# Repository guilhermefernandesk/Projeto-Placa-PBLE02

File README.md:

# Projeto-Placa-PBLE02
O projeto consiste na montagem de uma placa realizada por alunos da unifei. Bem como suas correções necessárias e simulação de uma aplicação via software na linguagem C.

## Autores:
<ul>
  <li> Eric Makiya Lazanha </li>
  <li> Guilherme Fernandes de Oliveira </li>
  <li> João Luiz de Miranda Cilli </li>
  <li> João Roberto da Silva Couto </li>
</ul>

## Imagens:

## Vídeo apresentação do projeto:
https://drive.google.com/file/d/1amIkBEUgF5RGjeDBrGX1CGrTWx1kXM-I/view?usp=sharing

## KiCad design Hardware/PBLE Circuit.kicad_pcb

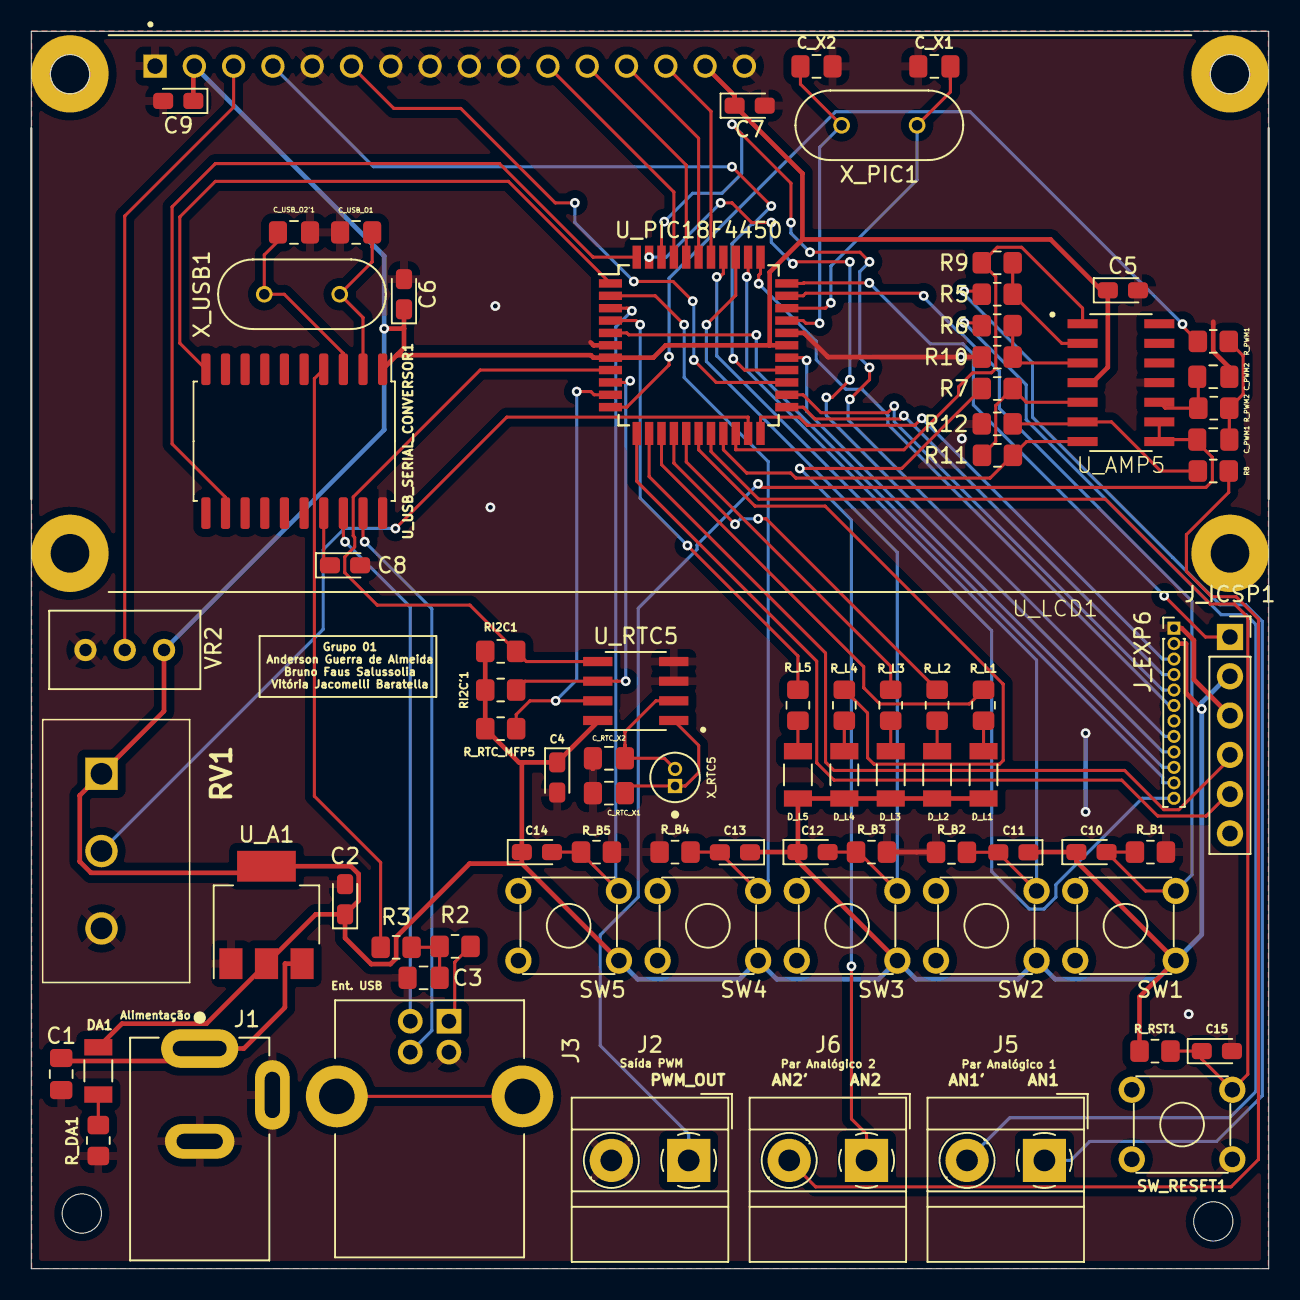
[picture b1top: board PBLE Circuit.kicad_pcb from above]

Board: 2 copper layers, 80.0 x 80.0 mm, 80 parts (0 on the bottom side), 71 nets.

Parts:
C1: 100n; C_0805_2012Metric_Pad1.18x1.45mm_HandSolder
C2, C4, C5, C6, C7, C8, C9, C10, C11, C12, C13, C14, C15: 10u; CP_EIA-2012-15_AVX-P_Pad1.30x1.05mm_HandSolder
C3: 100nF; C_0805_2012Metric_Pad1.18x1.45mm_HandSolder
C_PWM1: 20p; C_0805_2012Metric_Pad1.18x1.45mm_HandSolder
C_PWM2: 39p; C_0805_2012Metric_Pad1.18x1.45mm_HandSolder
C_RTC_X1, C_RTC_X2: 22pF; C_0805_2012Metric_Pad1.18x1.45mm_HandSolder
C_USB_O1, C_USB_O2'1: 22pF; C_0805_2012Metric_Pad1.18x1.45mm_HandSolder
C_X1, C_X2: 15pF; C_0805_2012Metric_Pad1.18x1.45mm_HandSolder
DA1: LED; LTST-C150GKT
D_L1, D_L2, D_L3, D_L4, D_L5: LED; LTST-C150GKT
J1: PJ-002A; CUI_PJ-002A
J2, J5, J6: Screw_Terminal_01x02; TerminalBlock_MetzConnect_Type011_RT05502HBWC_1x02_P5.00mm_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
J3: USB_B; USB_B_Lumberg_2411_02_Horizontal
J_EXP6: Conn_01x12_Male; PinHeader_1x12_P1.00mm_Vertical
J_ICSP1: Conn_01x06; PinSocket_1x06_P2.54mm_Vertical
R2, R5, R6, R7, R8: 10k; R_0805_2012Metric_Pad1.20x1.40mm_HandSolder
R3: 470; R_0805_2012Metric_Pad1.20x1.40mm_HandSolder
R9, R10, R11, R12: 2k4; R_0805_2012Metric_Pad1.20x1.40mm_HandSolder
RI2C1, RI2C'1: 4k7; R_0805_2012Metric_Pad1.20x1.40mm_HandSolder
RV1: R_POT; P160KN-0QC15B100K
R_B1, R_B2, R_B3, R_B4, R_B5: 4k7; R_0805_2012Metric_Pad1.20x1.40mm_HandSolder
R_DA1: 330; R_0805_2012Metric_Pad1.20x1.40mm_HandSolder
R_L1, R_L2, R_L3, R_L4, R_L5: 4k7; R_0805_2012Metric_Pad1.20x1.40mm_HandSolder
R_PWM1, R_PWM2: 20k; R_0805_2012Metric_Pad1.20x1.40mm_HandSolder
R_RST1: 4k7; R_0805_2012Metric_Pad1.20x1.40mm_HandSolder
R_RTC_MFP5: 10k; R_0805_2012Metric_Pad1.20x1.40mm_HandSolder
SW1, SW2, SW3, SW4, SW5: 1825910-6; SW_TH_Tactile_Omron_B3F-10xx
SW_RESET1: 1825910-6; SW_TH_Tactile_Omron_B3F-10xx
U_A1: LD1117S50TR_SOT223; SOT-223-3_TabPin2
U_AMP5: LM324DG
U_LCD1: LCD2X16; JHD162A
U_PIC18F4450: PIC18F4550-IPT; TQFP-44_10x10mm_P0.8mm
U_RTC5: MCP7940N-xSN; MCP7940N
U_USB_SERIAL_CONVERSOR1: MCP2200-I-SO; SOIC-20W_7.5x12.8mm_P1.27mm
VR2: 3296W-1-103RLF; Potentiometer_Bourns_3296W_Vertical
X_PIC1: ATS20A
X_RTC5: AB38T-32.768KHZ; AB38T
X_USB1: ATS12A

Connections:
+5V: C2.1, C4.1, C5.1, C6.1, C7.1, C9.1, C10.1, C11.1, C12.1, C13.1, C14.1, DA1.2 (A), D_L1.2 (A), D_L2.2 (A), D_L3.2 (A), D_L4.2 (A), D_L5.2 (A), J_EXP6.2, J_ICSP1.2, RI2C1.1, RI2C'1.1, RV1.1, R_RST1.1, R_RTC_MFP5.2, SW1.1, SW2.1, SW3.1, SW4.1, SW5.1, U_A1.2 (VO), U_AMP5.4 (VCC), U_LCD1.2 (VDD), U_LCD1.15 (LEDA), U_PIC18F4450.7 (VDD), U_PIC18F4450.28 (VDD), U_RTC5.8 (VCC), U_USB_SERIAL_CONVERSOR1.1 (VDD), VR2.3
/Alimentação/D+: J3.3 (D+), U_USB_SERIAL_CONVERSOR1.19 (D+)
/Alimentação/D-: J3.2 (D-), U_USB_SERIAL_CONVERSOR1.18 (D-)
/Alimentação/MCP_RST: R3.1, U_USB_SERIAL_CONVERSOR1.4 (RST)
/Interação com o usuário/B1: C10.2, R_B1.2, SW1.3, U_PIC18F4450.32 (T1OSO/T13CKI/RC0)
/Interação com o usuário/B2: C11.2, R_B2.2, SW2.3, U_PIC18F4450.35 (~UOE/CCP2/T1OSI/RC1)
/Interação com o usuário/B3: C12.2, R_B3.2, SW3.3, U_PIC18F4450.36 (P1A/CCP1/RC2)
/Interação com o usuário/B4: C13.2, R_B4.2, SW4.3, U_PIC18F4450.2 (SPP4/RD4)
/Interação com o usuário/B5: C14.2, R_B5.2, SW5.3, U_PIC18F4450.3 (P1B/SPP5/RD5)
/Interação com o usuário/L1: R_L1.1, U_PIC18F4450.14 (RB4/AN11/KBI0/CSSPP)
/Interação com o usuário/L2: R_L2.1, U_PIC18F4450.15 (RB5/KBI1/PGM)
/Interação com o usuário/L3: R_L3.1, U_PIC18F4450.16 (RB6/KBI2/PGC)
/Interação com o usuário/L4: R_L4.1, U_PIC18F4450.17 (RB7/KBI3/PGD)
/Interação com o usuário/L5: R_L5.1, U_PIC18F4450.4 (P1C/SPP6/RD6)
/Interação com o usuário/LCD.DB4: U_LCD1.11 (DB4), U_PIC18F4450.41 (SPP3/RD3)
/Interação com o usuário/LCD.DB5: U_LCD1.12 (DB5), U_PIC18F4450.40 (SPP2/RD2)
/Interação com o usuário/LCD.DB6: U_LCD1.13 (DB6), U_PIC18F4450.39 (SPP1/RD1)
/Interação com o usuário/LCD.DB7: U_LCD1.14 (DB7), U_PIC18F4450.38 (SPP0/RD0)
/Interação com o usuário/LCD.E: U_LCD1.6 (E), U_PIC18F4450.25 (CK1SPP/AN5/RE0)
/Interação com o usuário/LCD.RS: U_LCD1.4 (RS), U_PIC18F4450.26 (CK2SPP/AN6/RE1)
/Interação com o usuário/POT.OUT: RV1.2, U_PIC18F4450.21 (RA2/AN2/Vref-/CVref)
/Operação/AN1: R9.1, U_AMP5.1 (OUT1), U_PIC18F4450.20 (RA1/AN1)
/Operação/AN2: R11.1, U_AMP5.7 (OUT2), U_PIC18F4450.19 (RA0/AN0)
/Operação/ICPORTS: J_EXP6.6, U_PIC18F4450.34 ((ICPORTS))
/Operação/ICRST: J_ICSP1.1, U_PIC18F4450.33 ((~ICRST/ICVpp))
/Operação/MFP: R_RTC_MFP5.1, U_PIC18F4450.10 (RB2/AN8/INT2/VMO), U_RTC5.7 (MFP)
/Operação/PWM: R_PWM1.2, U_PIC18F4450.11 (RB3/AN9/CCP2/VPO)
/Operação/RA3: J_EXP6.3, U_PIC18F4450.22 (RA3/AN3/Vref+)
/Operação/RA4: J_EXP6.4, U_PIC18F4450.23 (RA4/T0CKI/C1OUT/RCV)
/Operação/RA5: J_EXP6.5, U_PIC18F4450.24 (RA5/AN4/~SS/HLVDIN/C2OUT)
/Operação/RC4: J_EXP6.8, U_PIC18F4450.42 (VM/D-/RC4)
/Operação/RC5: J_EXP6.9, U_PIC18F4450.43 (VP/D+/RC5)
/Operação/RD7: J_EXP6.11, U_PIC18F4450.5 (P1D/SPP7/RD7)
/Operação/RE2: J_EXP6.10, U_PIC18F4450.27 (OESPP/AN7/RE2)
/Operação/SCL: RI2C'1.2, U_PIC18F4450.9 (RB1/AN10/INT1/SCK/SCL), U_RTC5.6 (SCL)
/Operação/SDA: RI2C1.2, U_PIC18F4450.8 (RB0/AN12/INT0/FLT0/SDI/SDA), U_RTC5.5 (SDA)
/Operação/VUSB': J_EXP6.12, U_PIC18F4450.37 (VUSB)
AN1: J5.1, R5.2
AN1': J5.2, R6.2
AN2: J6.1, R7.2
AN2': J6.2, R8.2
A_IN+: R6.1, R10.2, U_AMP5.3 (IN1)
A_IN-: R5.1, R9.2, U_AMP5.2 (IN1)
B_IN+: R8.1, R12.2, U_AMP5.6 (IN2)
B_IN-: R7.1, R11.2, U_AMP5.5 (IN2)
CLK0: C_X1.1, U_PIC18F4450.31 (RA6/OSC2/CLKO), X_PIC1.1
CLK1: C_X2.1, U_PIC18F4450.30 (OSC1/CLKI), X_PIC1.2
C_IN+: C_PWM2.2, R_PWM2.1, U_AMP5.10 (IN3)
GNDREF: C1.2, C2.2, C3.1, C4.2, C5.2, C6.2, C7.2, C8.2, C9.2, C15.2, C_PWM2.1, C_RTC_X1.2, C_RTC_X2.2, C_USB_O1.2, C_USB_O2'1.2, C_X1.2, C_X2.2, J1.2, J1.3, J2.2, J3.4 (GND), J_EXP6.1, J_ICSP1.3, R10.1, R12.1, RV1.3, R_B1.1, R_B2.1, R_B3.1, R_B4.1, R_B5.1, R_DA1.2, SW_RESET1.1, U_A1.1 (GND), U_AMP5.11 (VEE,_GND), U_LCD1.1 (VSS), U_LCD1.5 (R/W), U_LCD1.7 (DB0), U_LCD1.8 (DB1), U_LCD1.9 (DB2), U_LCD1.10 (DB3), U_LCD1.16 (LEDK), U_PIC18F4450.6 (VSS), U_PIC18F4450.29 (VSS), U_RTC5.3 (VBAT), U_RTC5.4 (VSS), U_USB_SERIAL_CONVERSOR1.20 (VSS), VR2.1
MCLR: C15.1, R_RST1.2, SW_RESET1.3, U_PIC18F4450.18 (Vpp/~MCLR/RE3)
unnamed: C3.2, R2.1, R3.2
unnamed: C8.1, U_USB_SERIAL_CONVERSOR1.17 (V_USB)
unnamed: C_PWM1.1, R_PWM1.1, R_PWM2.2
unnamed: DA1.1 (K), R_DA1.1
unnamed: D_L1.1 (K), R_L1.2
unnamed: D_L2.1 (K), R_L2.2
unnamed: D_L3.1 (K), R_L3.2
unnamed: D_L4.1 (K), R_L4.2
unnamed: D_L5.1 (K), R_L5.2
unnamed: J3.1 (VBUS), R2.2
unnamed: U_LCD1.3 (VO), VR2.2
PGC: J_ICSP1.5, U_PIC18F4450.12 ((ICCK/ICPGC))
PGD: J_ICSP1.4, U_PIC18F4450.13 ((ICDT/ICPGD))
PWM_OUT: C_PWM1.2, J2.1, U_AMP5.8 (OUT3), U_AMP5.9 (IN3)
USB.O1: C_USB_O1.1, U_USB_SERIAL_CONVERSOR1.2 (OSC1), X_USB1.1
USB.O2: C_USB_O2'1.1, U_USB_SERIAL_CONVERSOR1.3 (OSC2), X_USB1.2
USB.RX: U_PIC18F4450.44 (TX/CK/RC6), U_USB_SERIAL_CONVERSOR1.12 (RX)
USB.TX: U_PIC18F4450.1 (SDO/RX/DT/RC7), U_USB_SERIAL_CONVERSOR1.10 (TX)
VCC: C1.1, J1.1, U_A1.3 (VI)
X1: C_RTC_X1.1, U_RTC5.1 (X1), X_RTC5.1
X2: C_RTC_X2.1, U_RTC5.2 (X2), X_RTC5.2

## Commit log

2025-11-23 Update images in README with markdown format
    Replaced old image links with new markdown image syntax.
